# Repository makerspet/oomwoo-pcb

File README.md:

<div align="center">

# OOMWOO I/O Board

*Open-source robot vacuum you build yourself.*

STM32G473 MCU · Motor drivers · Sensors · 4S charging · Smartphone compute (v1) · Raspberry Pi CM4/CM5 (planned) · KiCad

</div>

Part of [OOMWOO open-source robot vacuum](https://github.com/makerspet/oomwoo) project.

Get [MCU firmware](https://github.com/makerspet/oomwoo-firmware/).

## Boards

I'm keeping the first board as simple as possible, so it can be built and tested sooner:

- **[`kicad/main-phone`](kicad/main-phone/README.md) - v1, in progress.** An Android phone is the compute, connected to the STM32 over USB-C. No Raspberry Pi, cameras, M.2, SD card, speaker or mopping. The STM32 runs every motor and sensor, including the LiDAR and the front ToF sensors, and forwards their data to the phone.
- **Raspberry Pi CM4/CM5 carrier - planned.** Its early schematic is no longer in this repo; the Pi is still in the plans: cameras, an NPU and always-on Wi-Fi come with it. The notes below describe this board.

Details for both are in the [I/O board spec](docs/SPEC.md). Symbol, footprint and 3D libraries shared by all boards are in [`kicad/lib`](kicad/lib). Each board folder keeps its schematic PDF and BOM in `output/`, e.g. [the v1 board schematic](kicad/main-phone/output/main-phone.pdf).

The v1 board comes with a **[charging-only dock](kicad/charging-dock/README.md)**: a USB-C PD charger in (any charger with 20 V), a CH32V003 MCU (Arduino core, ch32fun, PlatformIO), robot detection before the contacts go live, and an IR beacon. The plan is to make the v1 board, the dock and the small sensor boards (including the two [front ToF boards](kicad/front/README.md), one design fitted twice, the [side sensor board](kicad/side/README.md) six [cliff sensor boards](kicad/cliff-sensor/README.md), the [rear docking IR board](kicad/rear/README.md) two [Hall sensor boards](kicad/hall-sensor/README.md) and the [wake-up sensor board](kicad/wake-sensor/README.md)) as one panel (V-cuts or mouse bites), so they share parts and cost less to make and ship. To keep part references unique across boards, every board has its own reference range: main board 1-999, dock 1000s, front ToF 2000s, side sensor 3000s, cliff 4000s, rear IR 5000s, Hall 6000s, wake-up sensor 7000s.

## Architecture notes

Consumer vacuums typically split compute into CPU and MCU. The MCU ([real examples](https://robotinfo.dev/)) controls
- all motors - driving wheels, suction fan, side brushes, mop motors, mop lift servos, pump and so on
- all sensors except below - IR cliff, IR side proximity, IR docking, wheel drop, bumper (IR or micro-switches), motor encoders, ultrasonic carpet sensor
- all push buttons
- 2D LiDAR motor RPM
- power - battery charging, motors power on/off
- all safety sensors - overcurrent for all motors (cheap vacuums ignore overcurrent sensing)

I/O board also provides audio encoders/decoders, amp, speaker (connector), mics (if any).

CPU receives
- 2D LiDAR data over serial port
- IMU (sometimes IMU gets forwarded via MCU) over SPI/I2C
- cameras (2x MIPI for visual obstacle avoidance)

MCU (and CPU) are usually always active. This allows the user to start cleaning at any time (especially via app remotely). Exceptions:
- no power (battery dead and no dock power)
- user explicitly shut down the vacuum by long-pressing the power button

The MCU's overarching constraint is to ensure robot safety. This is necessary to pass CE mark tests. Here is how MCU ensures safety:
- MCU firmware uses FreeRTOS or similar, static memory allocation, watchdog, guaranteed reaction time
- MCU acts as watchdog for CPU, resets CPU if CPU becomes unresponsive
- MCU connects to CPU over serial using a custom serial protocol ([concrete example](https://github.com/codetiger/VacuumRobot)). No micro-ROS to reduce dependencies, prevent bugs from updated 3rd party libraries slipping into safety-critical MCU firmware.
- MCU shuts down some (or all) motors when MCU detects overcurrent (brush stuck)
- MCU shuts down all motors (including power to all motors) when CPU becomes unresponsive (to prevent CPU sending garbage commands to MCU)
- MCU monitors battery charging, shuts it down when needed (battery too hot)
- MCU stops driving wheel motors when bumper sensors activate
- MCU tests motors, sensors
- MCU does not depend on CPU
- MCU toggles watchdog GPIO; otherwise an external-to-MCU circuit shuts down motor power

Consumer vacuums place CPU and MCU on the same PCB board. Since OOMWOO has to be hackable, it seems best to separate I/O from the compute. Therefore, this I/O board needs to have
- MCU and programming header
  - STM32G473VCT6 (LQFP-100): enough GPIOs, timers and ADCs for every motor and sensor, built-in op-amps for the carpet sensor echo, a USB device port and an RTC, in a hand-solderable package
  - see the [I/O board spec](docs/SPEC.md)
- all vacuum motor drivers (with connectors), driven by the MCU
  - cliff, side proximity, docking, bumper, carpet, water tank full/empty, dust bin present, motor overcurrent, motor encoders
- MCU connected to all sensors (except those handled by CPU like LiDAR serial, MIPI cameras I/O, IMU); sensor connectors
- control circuit for 2D LiDAR's motor (controlled by MCU)
- battery charging, power management (motors power on/off, charging on/off, power shut down), power for CPU compute module (see below)
- push buttons (home, power, etc.) and UI LEDs
- dock connector (dock power, sense dock present)
- USB power for charging; USB for serial shell, etc.
- audio encoder/decoder, audio amp, mics (if any)
- SD card for hacking, cheap large storage

Consumer vacuums usually don't have a CPU fan/heatsink because the vacuum's suction fan can (indirectly) cool the CPU/MCU PCB. Therefore, no CPU fan on this I/O board.

As far as compute - currently it seems best to use a Raspberry Pi CM4/CM5 compute module. Why?
- CM4/CM5 modules cost a bit less than a full Raspberry Pi 4/5
- CM4/CM5 have lower profile/height vs a full Raspberry Pi 4/5, important to keep vacuum cleaner slim
- there are plenty of 3rd party compute modules pin-compatible with CM4/CM5, making the compute swappable, hackable
  - 3rd party compute modules with NPUs are especially interesting because we need NPU for real-time camera-based obstacle detection

Compute module headers should expose
- 2x MIPI camera I/O
- 1x serial for CPU-MCU comms
- 1x serial for CPU-LiDAR comms
- 1x SPI (or I2C) for CPU-IMU comms
- audio (digital?) I/O
- power from I/O board to CM
- a few TBD GPIOs
  - MCU GPIO to reset CPU

This board should be designed using an open-source PCB tool (KiCad seems like a good choice).

## No manufacturing support

These designs are shared as-is, for reference and for your own work. I don't support manufacturing them: I can't help with ordering (JLCPCB or otherwise), out-of-stock parts, part substitutions, or troubleshooting boards built by others.

## License

[Apache License 2.0](LICENSE).

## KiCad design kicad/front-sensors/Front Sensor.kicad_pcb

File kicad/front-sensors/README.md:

# OOMWOO front ToF board

A small breakout for one VL53L7 8x8-zone time-of-flight sensor, one dock-homing IR receiver and a white torch LED. The robot fits two of them, from the same design: the left board aims 30° left and the right board 30° right, which together cover ~126° in front of the robot. Each board plugs into the [main board](../main-phone/README.md) (J6 or J5) through a 2x4 board-to-board connector, no cable (a 7-pin cable until 2026-11-06). Rev 2, 2026-10-27.

The dock-homing IR receivers were on this project until rev 2, then on the main board (U24, U25) from 2026-10-27. Since 2026-11-11 they are back here, one per board (U2002), so the receiver and the ToF sensor share one bumper opening: a bumper printed in pigmented filament blocks NIR, so both need an opening, and one is smaller than two.

## Circuit

- U2001: VL53L7CH (LCSC C19183986). The VL53L7CX (C5270520) and the VL53L5CX (C3178303, narrower 63° diagonal field of view) use the same footprint and pinout. Pin handling follows the datasheet (DS13865, table 3): RSVD1-4 to GND, RSVD5 not connected, RSVD6 47k pull-up (R2001), thermal pad to GND.
- AVDD (the analog and laser supply, rail VAA-3V3) gets its 3.3 V from VDD-3V3 through L2001 (BLM18PG121SN1D ferrite), so the laser current pulses stay off the shared 3.3 V. Each supply pin has 10 µF + 100 nF: C2001/C2002 on AVDD, C2003/C2004 on IOVDD. Place each pair right at its pins.
- U2002: Everlight IRM-H638T/TR2 (C91447), a 38 kHz IR receiver for the dock beacon, the same part as on the side board and the dock. It is top-looking (the lens is on its top face), and this board stands upright facing forward, so it looks forward too. Supply filter per the datasheet: R2002 100 Ω + C2005 10 µF. The output has an internal pull-up and goes straight to the MCU (U13: left board PE4, right board PE5).
- The VL53L7 INT pin is not wired to the connector (since 2026-11-11): firmware polls the sensor for new data, and J2001 pin 5 carries the IR receiver output instead. INT goes to test pad TP2001 (1 mm), since the sensor is leadless, for anyone who wants to experiment with it. It is open drain, so add a pull-up (for example 47k to 3.3 V) when you use it.
- LPn and I2C_RST stay on this board (since 2026-11-23): R2003 (47k) pulls LPn up to IOVDD and R2004 (47k) pulls I2C_RST down, as the datasheet asks, so the sensor is always enabled and its I2C interface never in reset. Firmware recovers a stuck bus with 9 clocks and a STOP, or by switching VSENS-3V3 off and on (the sensor firmware then has to be uploaded again).
- The I2C pull-ups stay on the main board (2.2k); with pull-ups on every board, a shared bus would be pulled up several times over.
- Each board has its own I2C bus (since 2026-11-23): the left board is on the main board's camera bus (CAM-SCL/CAM-SDA), the right board on the main bus (SCL/SDA). Both sensors start at the default address 0x52 and the left one keeps it. On the main bus the side VL53L0X also starts at 0x52, so at boot firmware holds it off with its XSHUT and moves the right VL53L7 to another address (lost on power-off, so every boot).
- Torch: LED2001, a XINGLIGHT XL-3030UWC-1W-3V white LED (C2843891, 6500K, 1 W 3030, 300 mA max), is the only torch part on this board since 2026-11-24: its driver moved to the main board to save space here. J2001 pin 6 is the anode (TORCH-A, from VSENS-5V-USB through the main board's R255 or R256, 10 Ω 1 W 2512) and pin 7 the cathode (TORCH-K, switched low-side by the main board's Q46, AO3400, PWM from U28 PB8; R257 100k holds it off in reset). About 190 mA at full duty (VF ~3.0–3.2 V), ~0.6 W in the LED, so give its pads copper. R2005 (10 Ω), Q2001 (AO3400), R2006 (100k) and C2006 (10 µF) were on this board until then. Firmware sets the brightness by PWM duty. A white LED puts out almost nothing at 940 nm, so it shouldn't disturb the ToF or the IR receiver.
- Parts use the JLC library symbols and footprints (JLCImport:C0603/R0603, 2026-11-05); LPn is named ~{LPn} (active low); a PWR_FLAG on VAA-3V3 clears the ERC error behind the ferrite.

## Connector J2001

Board-to-board, no cable (since 2026-11-06). The board hangs under the main board, upright, and plugs straight into it:

- J2001 (this board): HanElectricity 2005WR-2x4P (C6837622), 2.0 mm 2x4 right-angle pin header, through hole, on the **back** of the board. The sensor is on the front, so the board can sit right at the main board's front edge and the main board stays out of the sensor's 60° x 60° field of view.
- J6 / J5 (main board): HanElectricity 2005FV-2x4P (C18723066), 2.0 mm 2x4 vertical socket, 4.3 mm tall, through hole, fitted on the main board's **underside**.
- A small mount screwed to the main board holds the ToF board upright and takes the load; the header only makes the contact.

| J2001 pin | Signal | Mates with socket pin |
| --- | --- | --- |
| 1 | 3.3 V | 2 |
| 2 | GND | 1 |
| 3 | SDA | 4 |
| 4 | SCL | 3 |
| 5 | IR_OUT (IR receiver; INT until 2026-11-11) | 6 |
| 6 | TORCH-A (torch LED anode, 5 V through R255/R256 on the main board; 5 V until 2026-11-24, I2C_RST until 2026-11-23) | 5 |
| 7 | TORCH-K (torch LED cathode, switched by Q46 on the main board; the PWM gate signal until 2026-11-24, ~LPn until 2026-11-23) | 8 |
| 8 | GND | 7 |

**Pin numbers don't match across the mating, on purpose.** On the right-angle header the odd row (1, 3, 5, 7) is the upper row, farther from the board face; mated with a socket on the main board's underside, the rows swap. The schematics already account for this, so this only holds if the socket is placed this way round:

- the socket's pin 1-2 end on the same side as the header's pin 1-2 end
- the socket's odd row (1, 3, 5, 7) toward the ToF board, the even row away from it

Rotated 180°, 3.3 V would meet GND, and 5 V would reach the sensor's I2C lines. Check both boards together in the 3D CAD before ordering, and mark pin 1 on both silkscreens.

## PCB notes (for layout)

- The PCB file in this folder is the old combined layout. Run *Update PCB from Schematic* before layout work.
- Keep the board small. No mounting holes (removed 2026-10-29): a mount screwed to the main board holds it upright, under the main board (designed with the 3D CAD; until 2026-11-06 the board slid into a holder by its long edges). The sensor looks out of the front face; J2001 sits on the back, at the edge that meets the main board.
- The sensor needs a clear view through the bumper window: no copper, silkscreen or part above it, and a cover window from a material on ST's cover-glass list.
- Put TP2001 on the back, away from the sensor's view. It has no paste and stays off the BOM.
- Torch LED2001: on the front face, aimed forward, outside the ToF's 60° x 60° field of view and away from U2002, behind its own bumper opening or diffuser. Light from it must not reach the ToF cover window from inside the bumper. Give LED2001's pads copper for heat.
- LED2001's footprint (`JLCImport:LED-3030_XL-3030UWC`) is ours, not JLC's: the datasheet's land pattern and JLC's footprint disagree on which of the LED's two terminals (0.7 mm and 2.0 mm wide) is which, and the wrong guess would let the wide terminal bridge both pads. Both pads are 1.13 mm wide with a 1.3 mm gap, so the LED solders safely either way; pad 1 is the cathode (the chamfered corner, pin 1 in the datasheet). Check a real part's terminals before ordering and, if confirmed, widen the pad under the wide terminal for heat.
- Place U2002 on the front face right next to the sensor, so one bumper opening covers both, and keep it and the baffle out of the sensor's 60° x 60° field of view. An opaque baffle between them (part of the mount or bumper) keeps the ToF laser off the receiver.
- Reference designators are in this board's 2000s range: every board has its own reference range: main board 1-999, dock 1000s, front ToF 2000s, side sensor 3000s, cliff 4000s, rear IR 5000s, Hall 6000s, wake-up sensor 7000s. The panel has two copies of this board; let KiKit (or the panel tool) rename references per copy so the assembly files stay unique.

## Assembly: the sensor is placed by hand

JLC assembles the passives and the connector; U2001 is left off (`in_bom no`, `in_pos_files no`) and placed and reflowed by hand. JLC's price for the sensor is high and stock is thin, while distributors are about $3 cheaper per sensor (2026-10-27, volume prices):

| Source | Part | Price |
| --- | --- | --- |
| JLC/LCSC | VL53L7CH / VL53L7CX | $11.46 (2 in stock) / $8.46 (77) |
| DigiKey | VL53L7CX / VL53L7CH | $6.06 / $6.21 at 1,000 |
| Mouser | VL53L7CX | $5.72 at 500, $5.17 at 3,600 |
| ST | VL53L7CH / VL53L5CX | $5.63 / $5.89 at 500 (tariffs not checked) |

The board is one-sided with a handful of parts, so a small home reflow oven handles it. The sensor is an LGA: use a stencil (order one with the boards) and check the pads for bridges under a magnifier before power-up.

## Open items

- Holder angle and the cover window material.

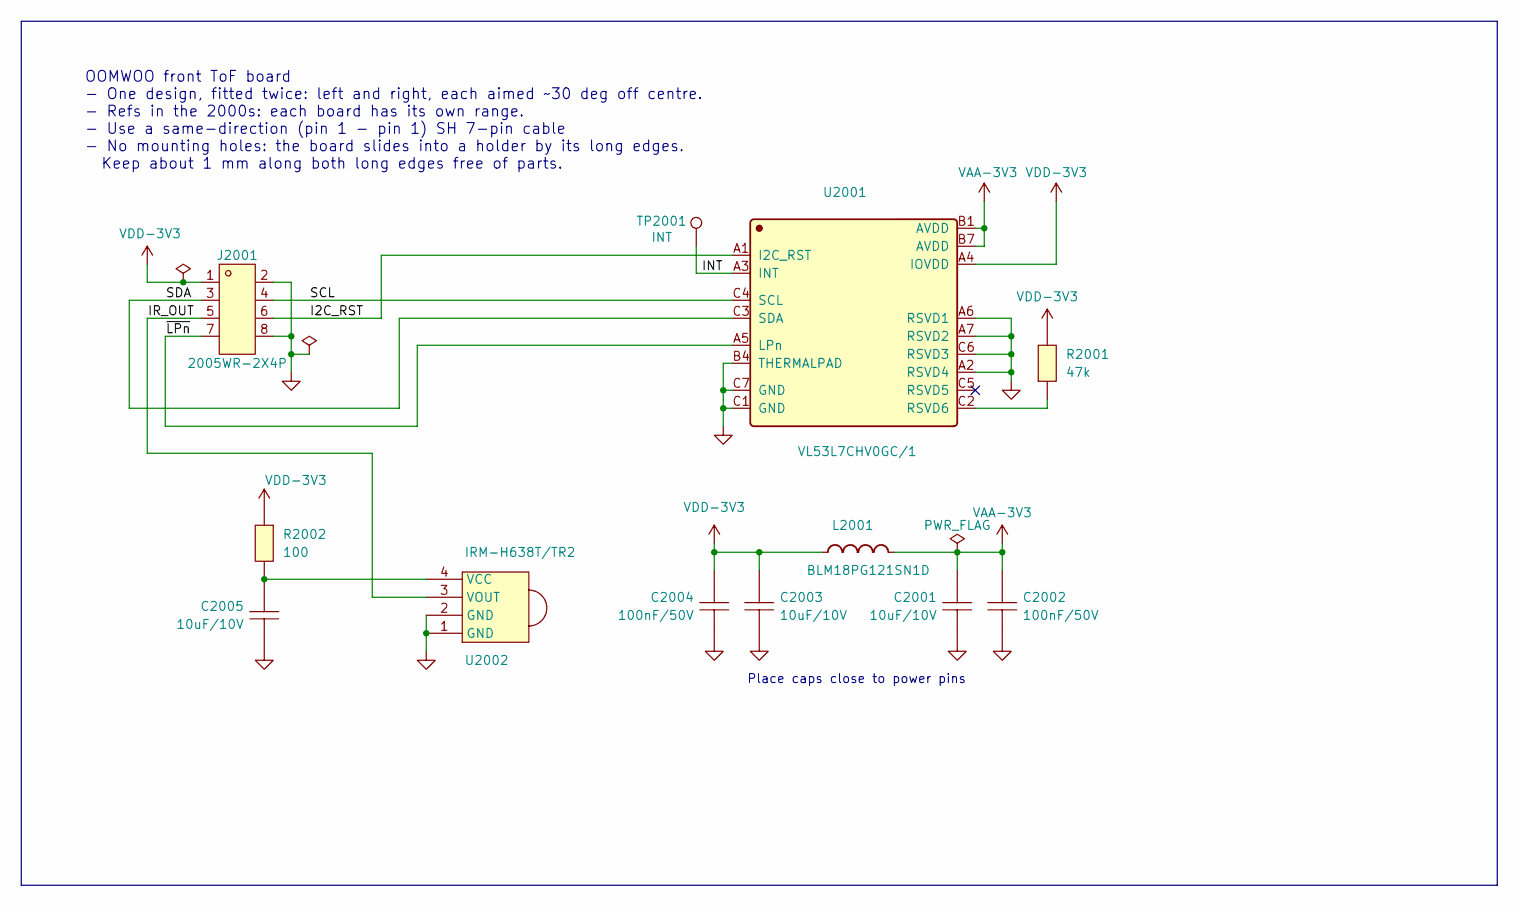
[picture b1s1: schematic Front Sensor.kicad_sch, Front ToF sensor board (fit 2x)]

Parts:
C2001, C2003, C2005: 10uF/10V; C0603; MPN CL10A106KP8NNNC; LCSC C19702
C2002, C2004: 100nF/50V; C0603; MPN CL10B104KB8NNNC; LCSC C1591
J2001: 2005WR-2X4P; HDR-TH_8P-P2.00-H-F-R2-C2-S2.00-W8.8; MPN 2005WR-2x4P; LCSC C6837622
L2001: BLM18PG121SN1D; Manufacturer Part BLM18PG121SN1D; LCSC C14709
R2001: 47k; R0603; MPN FRC0603F4702TS; LCSC C2907042
R2002: 100; R0603; MPN FRC0603F1000TS; LCSC C2906981
TP2001: INT; TestPoint_Pad_D1.0mm
U2001: VL53L7CHV0GC/1; VL53L7CHV0GC_1; LCSC C19183986
U2002: IRM-H638T/TR2; IRM-H638T; LCSC C91447

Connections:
/I2C_RST: J2001.6, U2001.A1 (I2C_RST)
/INT: TP2001.1 (1_1), U2001.A3 (INT)
/IR_OUT: J2001.5, U2002.3 (VOUT)
/SCL: J2001.4, U2001.C4 (SCL)
/SDA: J2001.3, U2001.C3 (SDA)
/~LPn: J2001.7, U2001.A5 (LPn)
GND: C2001.2, C2002.2, C2003.2, C2004.2, C2005.2, J2001.2, J2001.8, U2001.A2 (RSVD4), U2001.A6 (RSVD1), U2001.A7 (RSVD2), U2001.B4 (THERMALPAD), U2001.C1 (GND), U2001.C6 (RSVD3), U2001.C7 (GND), U2002.1 (GND), U2002.2 (GND)
unnamed: R2001.1, U2001.C2 (RSVD6)
unnamed: C2005.1, R2002.2, U2002.4 (VCC)
VAA-3V3: C2001.1, C2002.1, L2001.2, U2001.B1 (AVDD), U2001.B7 (AVDD)
VDD-3V3: C2003.1, C2004.1, J2001.1, L2001.1, R2001.2, R2002.1, U2001.A4 (IOVDD)

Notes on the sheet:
Place caps close to power pins
OOMWOO front ToF board - One design, fitted twice: left and right, each aimed ~30 deg off centre. - Refs in the 2000s: each board has its own range. - Use a same-direction (pin 1 - pin 1) SH 7-pin cable - No mounting holes: the board slides into a holder by its long edges. Keep about 1 mm along bot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

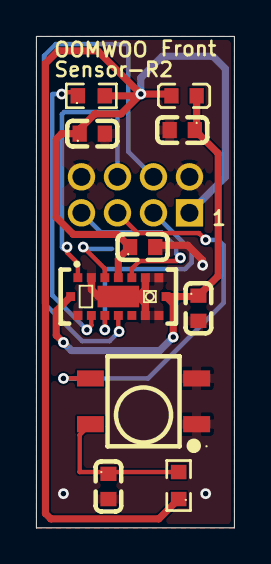
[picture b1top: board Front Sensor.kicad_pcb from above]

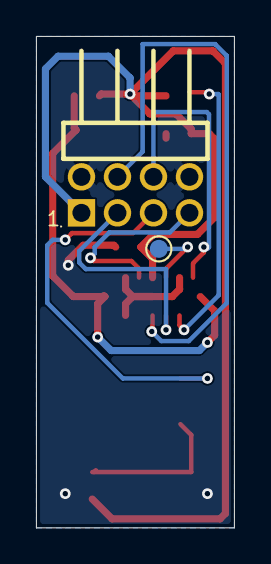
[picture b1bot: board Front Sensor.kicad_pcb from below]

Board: 2 copper layers, 11.0 x 27.3 mm, 12 parts (2 on the bottom side), 11 nets.

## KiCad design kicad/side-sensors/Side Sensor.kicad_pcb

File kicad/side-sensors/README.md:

# OOMWOO side sensor board

A small board on the robot's right side, for wall-following and for spotting the dock while driving past it. It plugs into the [main board](../main-phone/README.md) (SIDE-R1) with a 7-pin cable. Rev 2, 2026-10-27. There is no left side sensor on v1.

Rev 1 had a VL6180 with a 2.8 V regulator and a TSOP38238. The VL6180 is NRND at ST (obsolete at DigiKey and Future), and its 2.8 V I/O sits at its limit on the robot's 3.3 V bus.

## Circuit

- U3001: VL53L0X (VL53L0CXV0DH/1, LCSC C91199, ~$1.63): single-zone time-of-flight distance sensor, runs from 3.3 V directly.
  - It reads poorly below ~3 cm, so the board sits a little recessed in the robot's side.
  - 10 µF + 100 nF (C3001/C3002) at its supply pins.
  - XSHUT has no pull-up since 2026-11-04 (R3001 removed): the MCU drives it (PE3), and the sensor rail is off whenever the MCU is in reset. GPIO1 (open drain, the interrupt) has no pull-up here since 2026-11-03: it joins the shared INT-SENSORS line on the main board, pulled up there by R2 (47k; R61 until 2026-11-11), so R3002 was in parallel with it and is removed. The I2C pull-ups (2.2k) are on the main board too.
  - Firmware: the I/Os run at 3.3 V (= AVDD), so set the ST API to 2V8 I/O mode (the API default is 1V8).
- U3002: Everlight IRM-H638T/TR2 (C91447, ~$0.13), a 38 kHz top-looking IR receiver (the lens is on its top face), the same part as the dock's U1202. It sees the dock's beacon when the robot passes alongside it. Supply filter per the datasheet: R3003 100 Ω + C3003 10 µF. The output has an internal pull-up.

Both parts look out of the board face, so the board mounts upright in the side of the robot, facing out.

## Connector J3001

ZX-SH1.0-7PWT (C7430449): JST SH compatible, 1.0 mm pitch, SMD, right angle. The main board's SIDE-R1 uses the same part.

| Pin | Signal | Main board |
| --- | --- | --- |
| 1 | 3.3 V | |
| 2 | GND | |
| 3 | IR_OUT | PD6 (USART2 RX) |
| 4 | GPIO1 (interrupt) | PD12, shared with the front ToF interrupts (open drain) |
| 5 | XSHUT | PE3 |
| 6 | SCL | I2C4 SCL (PC6) |
| 7 | SDA | I2C4 SDA (PC7) |
| 8, 9 | mounting pads, GND | |

Use a pin 1 to pin 1 cable and mark pin 1 on the silkscreen of both boards.

The VL53L0X starts at I2C address 0x52, the same as the two front VL53L7s on the same bus. Only the left VL53L7's LPn is on the MCU, so XSHUT takes part in addressing: at boot, hold the left LPn and XSHUT low, so only the right VL53L7 answers, and move it to a new address. Release the left LPn and move the left sensor, then release XSHUT; the VL53L0X can keep 0x52. XSHUT also resets a stuck sensor.

## PCB notes (for layout)

- The PCB file in this folder is the old layout. Run *Update PCB from Schematic* before layout work.
- H3001/H3002: two M2 holes (`MountingHole_2.2mm_M2_Pad`, pads to GND, not in the BOM), to keep the board small.
- Keep copper, silkscreen and parts out of the sensor's field of view, and give it a cover window (ST's cover-glass guidance applies).
- Reference designators are in this board's 3000s range: every board has its own reference range: main board 1-999, dock 1000s, front ToF 2000s, side sensor 3000s, cliff 4000s, rear IR 5000s, Hall 6000s, wake-up sensor 7000s.

All parts are assembled at JLC.

Symbols and footprints come from the shared libraries in [`../lib`](../lib) (`JLCImport`) and the KiCad standard libraries.

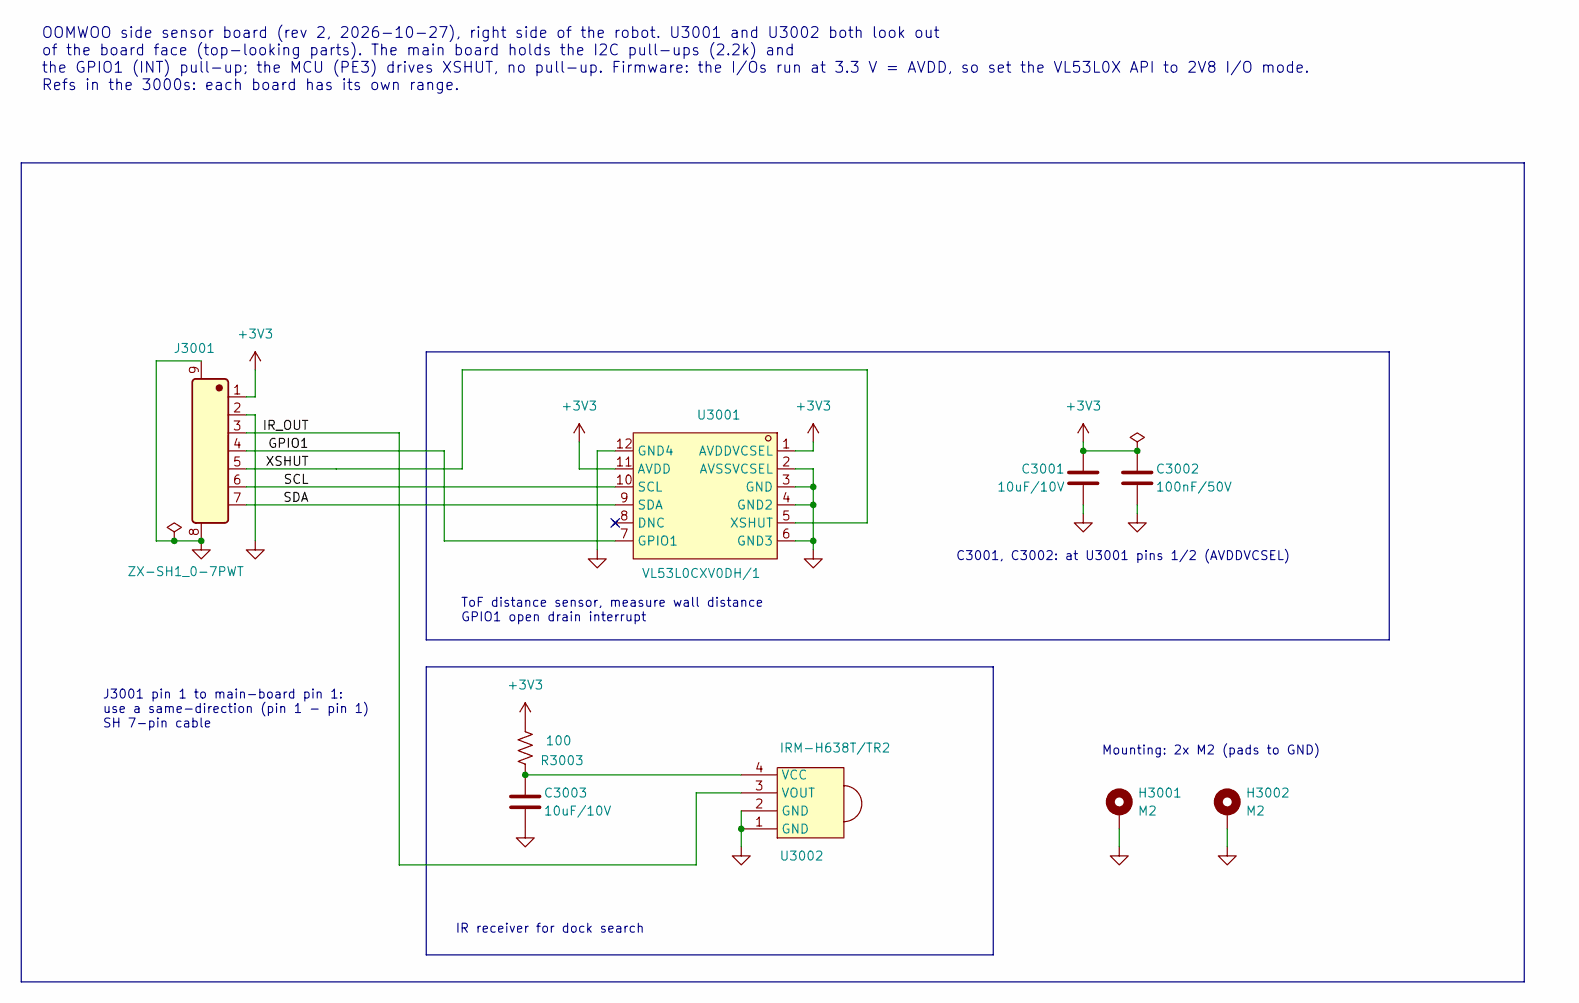
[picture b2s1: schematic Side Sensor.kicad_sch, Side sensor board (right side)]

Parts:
C3001, C3003: 10uF/10V; C_0603_1608Metric; LCSC C19702
C3002: 100nF/50V; C_0603_1608Metric; LCSC C1591
H3001, H3002: M2; MountingHole_2.2mm_M2_Pad
J3001: ZX-SH1_0-7PWT; LCSC C7430449
R3003: 100; R_0603_1608Metric; LCSC C2906981
U3001: VL53L0CXV0DH/1; VL53L0CXV0DH_1; LCSC C91199
U3002: IRM-H638T/TR2; IRM-H638T; LCSC C91447

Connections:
+3V3: C3001.1, C3002.1, J3001.1, R3003.1, U3001.1 (AVDDVCSEL), U3001.11 (AVDD)
/GPIO1: J3001.4, U3001.7 (GPIO1)
/IR_OUT: J3001.3, U3002.3 (VOUT)
/SCL: J3001.6, U3001.10 (SCL)
/SDA: J3001.7, U3001.9 (SDA)
/XSHUT: J3001.5, U3001.5 (XSHUT)
GND: C3001.2, C3002.2, C3003.2, H3001.1 (1_1), H3002.1 (1_1), J3001.2, J3001.8, J3001.9, U3001.2 (AVSSVCSEL), U3001.3 (GND), U3001.4 (GND2), U3001.6 (GND3), U3001.12 (GND4), U3002.1 (GND), U3002.2 (GND)
unnamed: C3003.1, R3003.2, U3002.4 (VCC)

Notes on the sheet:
Mounting: 2x M2 (pads to GND)
C3001, C3002: at U3001 pins 1/2 (AVDDVCSEL)
ToF distance sensor, measure wall distance GPIO1 open drain interrupt
IR receiver for dock search
OOMWOO side sensor board (rev 2, 2026-10-27), right side of the robot. U3001 and U3002 both look out of the board face (top-looking parts). The main board holds the I2C pull-ups (2.2k) and the GPIO1 (INT) pull-up; the MCU (PE3) drives XSHUT, no pull-up. Firmware: the I/Os run at 3.3 V = AVDD, so se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
J3001 pin 1 to main-board pin 1: use a same-direction (pin 1 - pin 1) SH 7-pin cable

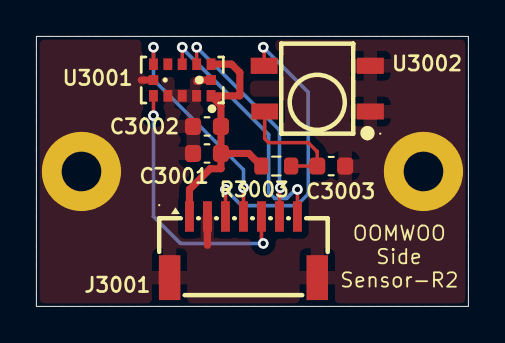
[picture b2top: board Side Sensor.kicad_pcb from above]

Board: 2 copper layers, 24.0 x 15.0 mm, 9 parts (0 on the bottom side), 8 nets.

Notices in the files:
README.md:
License: Apache-2.0
